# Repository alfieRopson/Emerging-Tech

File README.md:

Collection of files as additional evidence for my Emerging Tech Brief.

This was created for files in connection with my fullfillment of he Emerging Tech Module as part of the 3rd year of my degree at Nottingham Trent University. If you aren't a tutor at NTU and you happen to find this because i've accidentally made it public then please feel free to use the code here if it's useful to you. If you are a tutor at NTU you have successfully found the right place.

MIDI_ultrasonic_trigger.ino Arduino Sketch for ultrasonic Triggers

alfie et.show.gz Dot2 showfile This can be viewed in the dot2 onpc software downloadable here: https://www.malighting.com/downloads/products/dot2/

Microsoft Projection Mapping.avc Resolume Showfile

midi theremin and ultrasonic trigger folders contain kicad project files

Plots and Reports contain Technical Documents produced

Microsoft Full production Spreadsheet contains the full production costing

Emerging Tech final invoice is the final invoice

Power Calculations Spreadsheet shows the power draw for each circuit

Rigging Calculations Spreadsheet contains the weight bearing calculations for the truss and motors

Link to Capture File https://myntuac-my.sharepoint.com/:u:/g/personal/n1067397_my_ntu_ac_uk/EfvAf5Dc8PdMnaO8TO10--gBLIG8ppxRylPfLy_TPjcecw?e=hPuOsN

Link to Video Assets https://myntuac-my.sharepoint.com/:f:/g/personal/n1067397_my_ntu_ac_uk/EuZve8bgMbRAsPguAyOVR-gBkFQ3IOzpsc9bqpKOynCcEA?e=M3Nbbo

Video Evidence:
  Cues 1-4 Youtube Playlist: https://www.youtube.com/playlist?list=PLZdywKp9EDC7ZR6HvclH-SQt3OLCKNzIM

  Trigger Demo Video: https://youtu.be/9YEa6ooch3k

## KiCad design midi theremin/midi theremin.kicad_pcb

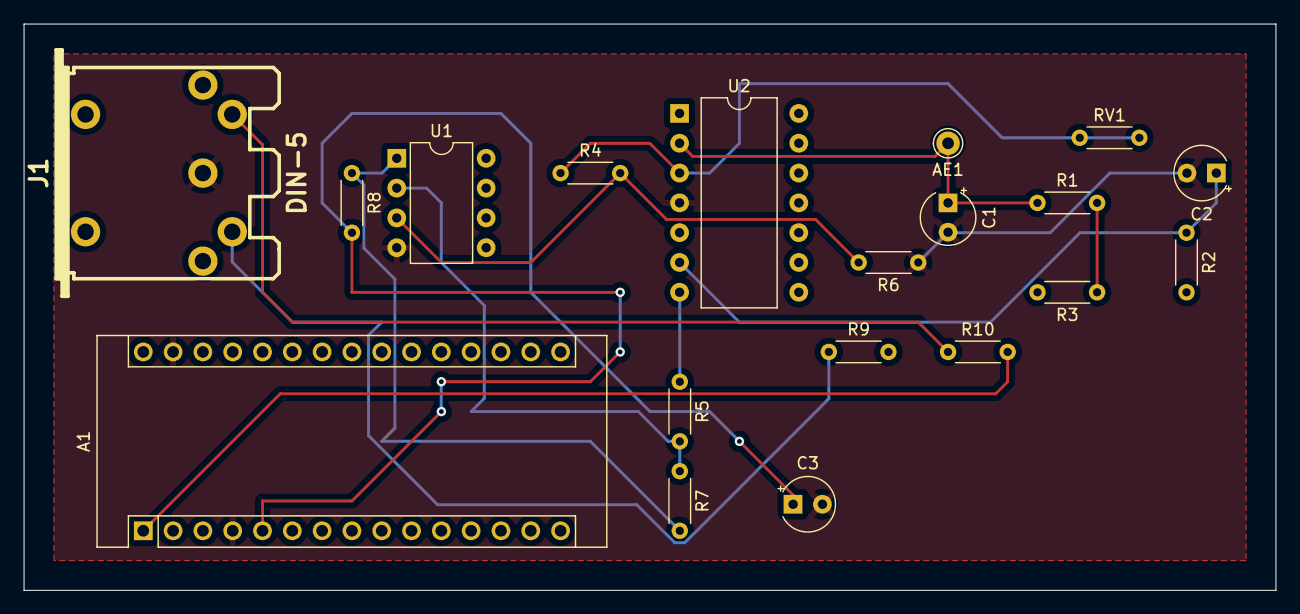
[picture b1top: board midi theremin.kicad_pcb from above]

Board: 2 copper layers, 106.7 x 48.3 mm, 19 parts (0 on the bottom side), 14 nets.

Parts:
A1: Arduino_Nano_v3.x; Arduino_Nano
AE1: Antenna; Pin_D1.0mm_L10.0mm
C1, C2: 100pF; CP_Radial_Tantal_D4.5mm_P2.50mm
C3: 1nF; CP_Radial_Tantal_D4.5mm_P2.50mm
J1: DIN-5
R1: 5K1; R_Axial_DIN0204_L3.6mm_D1.6mm_P5.08mm_Horizontal
R2, R3, R4, R5, R6, R7: 10K; R_Axial_DIN0204_L3.6mm_D1.6mm_P5.08mm_Horizontal
R8: 6K8; R_Axial_DIN0204_L3.6mm_D1.6mm_P5.08mm_Horizontal
R9, R10: 220R; R_Axial_DIN0204_L3.6mm_D1.6mm_P5.08mm_Horizontal
RV1: 10K; R_Axial_DIN0204_L3.6mm_D1.6mm_P5.08mm_Horizontal
U1: MCP602; DIP-8_W7.62mm
U2: CD4093; DIP-14_W10.16mm

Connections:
+5V: A1.27 (+5V), R9.2, U1.8 (V+), U2.1, U2.5
GND: A1.4 (GND), A1.29 (GND), C1.2, C2.2, C3.2, J1.2, R6.1, U1.4 (V-), U2.4 (GND)
unnamed: A1.5 (D2), C3.1, R8.2
unnamed: AE1.1 (A), C1.1, R1.1, U2.2
unnamed: C2.1, R2.1, U2.6
unnamed: J1.4, R9.1
unnamed: J1.5, R10.1
unnamed: R1.2, R3.1
unnamed: R3.2, R5.1, U2.7
unnamed: R4.1, RV1.1, RV1.2, U2.3
unnamed: R4.2, R6.2, U1.3 (+)
unnamed: R5.2, R7.1, U1.2 (-)
unnamed: R7.2, R8.1, U1.1
midi out: A1.1 (D1/TX), R10.2
